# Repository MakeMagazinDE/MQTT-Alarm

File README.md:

Maker Media GmbH

***

# MQTT-Alarm, Make 4/21
Software und Platinen für Alarm-Kontakt und Alarm-Zentrale

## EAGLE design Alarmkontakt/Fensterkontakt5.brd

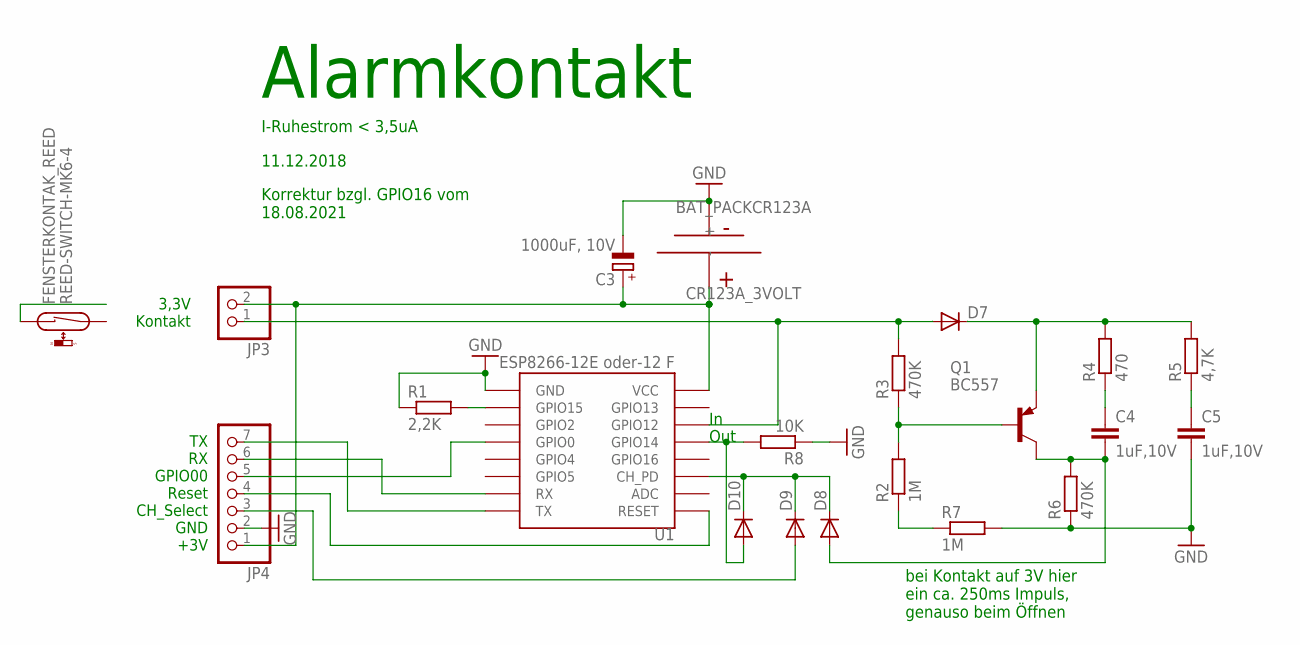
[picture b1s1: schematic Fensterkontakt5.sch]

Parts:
C3: 1000uF, 10V; E5-4
C4, C5: 1uF,10V; C075-032X103
CR123A_3VOLT: BAT_PACKCR123A; BH123A
D7, D8, D9, D10: DIODE-D-7.5; D-7.5
FENSTERKONTAK_REED: REED-SWITCH-MK6-4; MK6-4
JP3: PINHD-1X2; 1X02
JP4: PINHD-1X7; 1X07
Q1: BC557; TO92-EBC
R1: 2,2K; 0207/7
R2, R7: 1M; 0207/7
R3, R6: 470K; 0207/7
R4: 470; 0207/7
R5: 4,7K; 0207/7
R8: 10K; 0207/7
U1: ESP8266-12E oder-12 F; ESP12

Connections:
GND: C3.-, C5.2, CR123A_3VOLT.-, JP4.2, R1.1, R6.1, R7.2, R8.1, U1.GND
unnamed: C4.2, D8.A, Q1.C, R6.2
unnamed: D7.C, Q1.E, R4.2, R5.2
unnamed: C5.1, R5.1
unnamed: JP4.7, U1.TX
unnamed: Q1.B, R2.2, R3.1
unnamed: D8.C, D9.C, D10.C, U1.CH_PD
unnamed: C4.1, R4.1
unnamed: D10.A, R8.2, U1.GPIO14
unnamed: JP4.6, U1.RX
unnamed: D7.A, JP3.1, R3.2, U1.GPIO12
unnamed: R1.2, U1.GPIO15
unnamed: JP4.4, U1.RESET
unnamed: D9.A, JP4.3
unnamed: C3.+, CR123A_3VOLT.+, JP3.2, JP4.1, U1.VCC
unnamed: R2.1, R7.1
unnamed: JP4.5, U1.GPIO0

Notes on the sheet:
3,3V Kontakt
I-Ruhestrom < 3,5uA
Alarmkontakt
11.12.2018
TX RX GPIO00 Reset CH_Select GND +3V
bei Kontakt auf 3V hier ein ca. 250ms Impuls, genauso beim Öffnen
Out
Korrektur bzgl. GPIO16 vom 18.08.2021

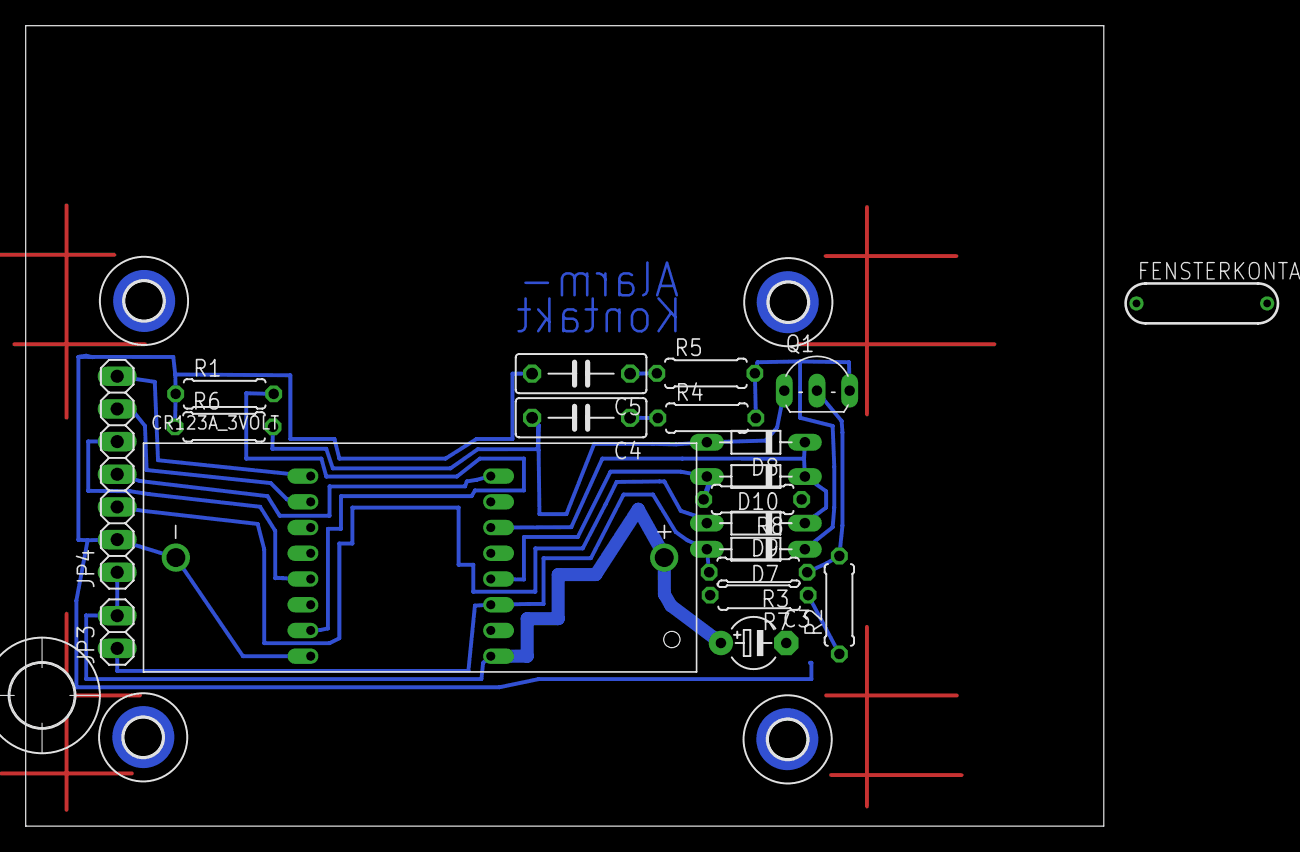
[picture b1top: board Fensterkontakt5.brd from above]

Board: 2 copper layers, 83.8 x 62.2 mm, 26 parts (1 on the bottom side), 17 nets.

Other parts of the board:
U$1: 5,0
U$2, U$3, U$4, U$5: 3,0

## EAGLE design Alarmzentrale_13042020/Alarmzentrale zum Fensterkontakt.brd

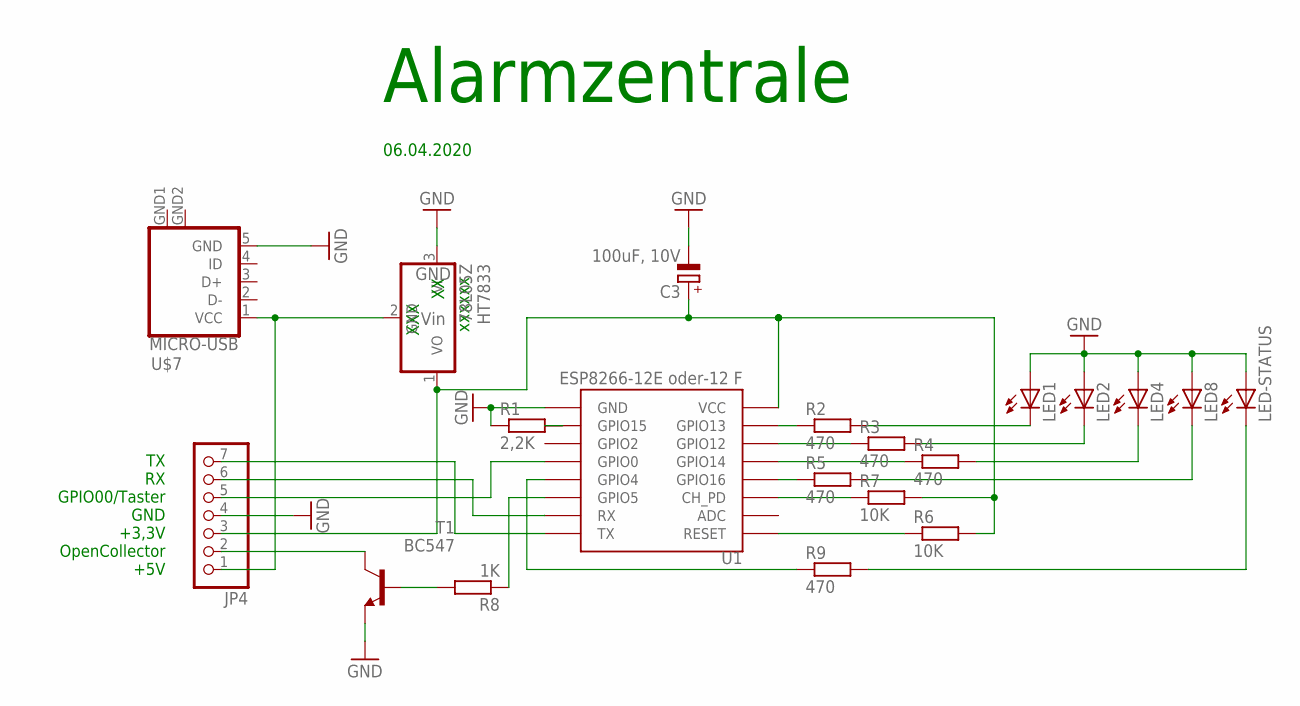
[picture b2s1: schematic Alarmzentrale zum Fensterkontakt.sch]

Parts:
C3: 100uF, 10V; E5-4
HT7833: 78L05Z; TO92
JP4: PINHD-1X7; 1X07
LED1, LED2, LED4, LED8: LED_ELD260; LED_LD260
LED-STATUS: LED_ELD260; LED_LD260
R1: 2,2K; 0207/7
R2, R3, R4, R5, R9: 470; 0207/7
R6, R7: 10K; 0207/7
R8: 1K; 0207/7
T1: BC547; TO92L
U1: ESP8266-12E oder-12 F; ESP12
U$7: MICRO-USB

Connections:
GND: C3.-, HT7833.3 (VI), JP4.4, LED1.A, LED2.A, LED4.A, LED8.A, LED-STATUS.A, R1.1, T1.1 (E), U1.GND, U$7.5 (GND), U$7.GND1 (GND), U$7.GND2 (GND)
unnamed: C3.+, HT7833.1 (VO), JP4.3, R6.2, R7.2, U1.VCC
unnamed: R2.1, U1.GPIO13
unnamed: R3.1, U1.GPIO12
unnamed: JP4.7, U1.TX
unnamed: R4.1, U1.GPIO14
unnamed: R5.1, U1.GPIO16
unnamed: R7.1, U1.CH_PD
unnamed: R6.1, U1.RESET
unnamed: R8.2, T1.2 (B)
unnamed: JP4.6, U1.RX
unnamed: LED1.K (C), R2.2
unnamed: R1.2, U1.GPIO15
unnamed: LED2.K (C), R3.2
unnamed: LED4.K (C), R4.2
unnamed: LED8.K (C), R5.2
unnamed: R9.1, U1.GPIO4
unnamed: HT7833.2 (GND), JP4.1, U$7.1 (VCC)
unnamed: JP4.2, T1.3 (C)
unnamed: LED-STATUS.K (C), R9.2
unnamed: R8.1, U1.GPIO5
unnamed: JP4.5, U1.GPIO0

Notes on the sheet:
Alarmzentrale
06.04.2020
TX RX GPIO00/Taster GND +3,3V OpenCollector +5V
GND
Vin
xxxxxx
XXX

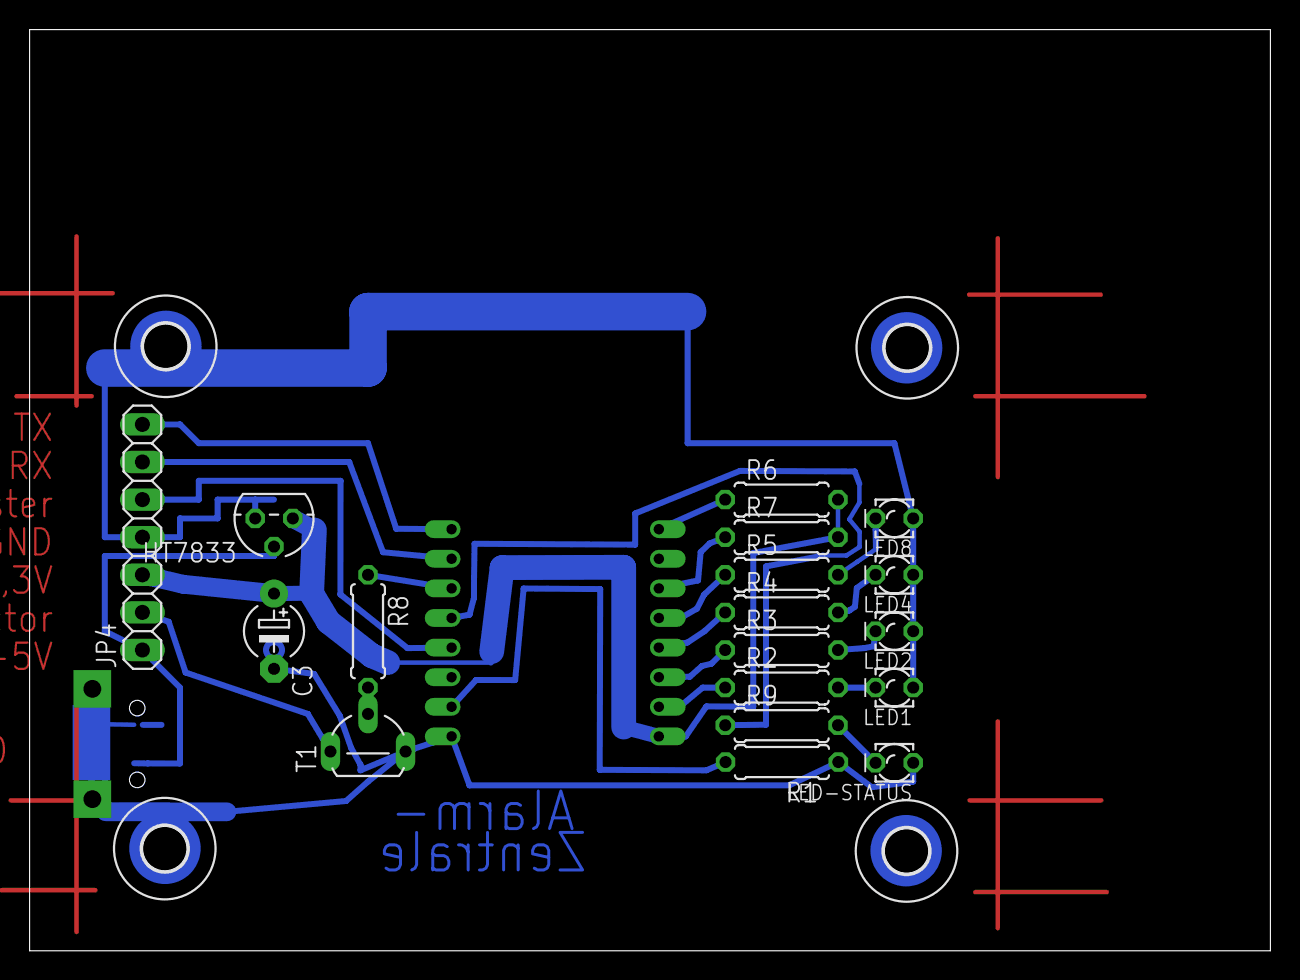
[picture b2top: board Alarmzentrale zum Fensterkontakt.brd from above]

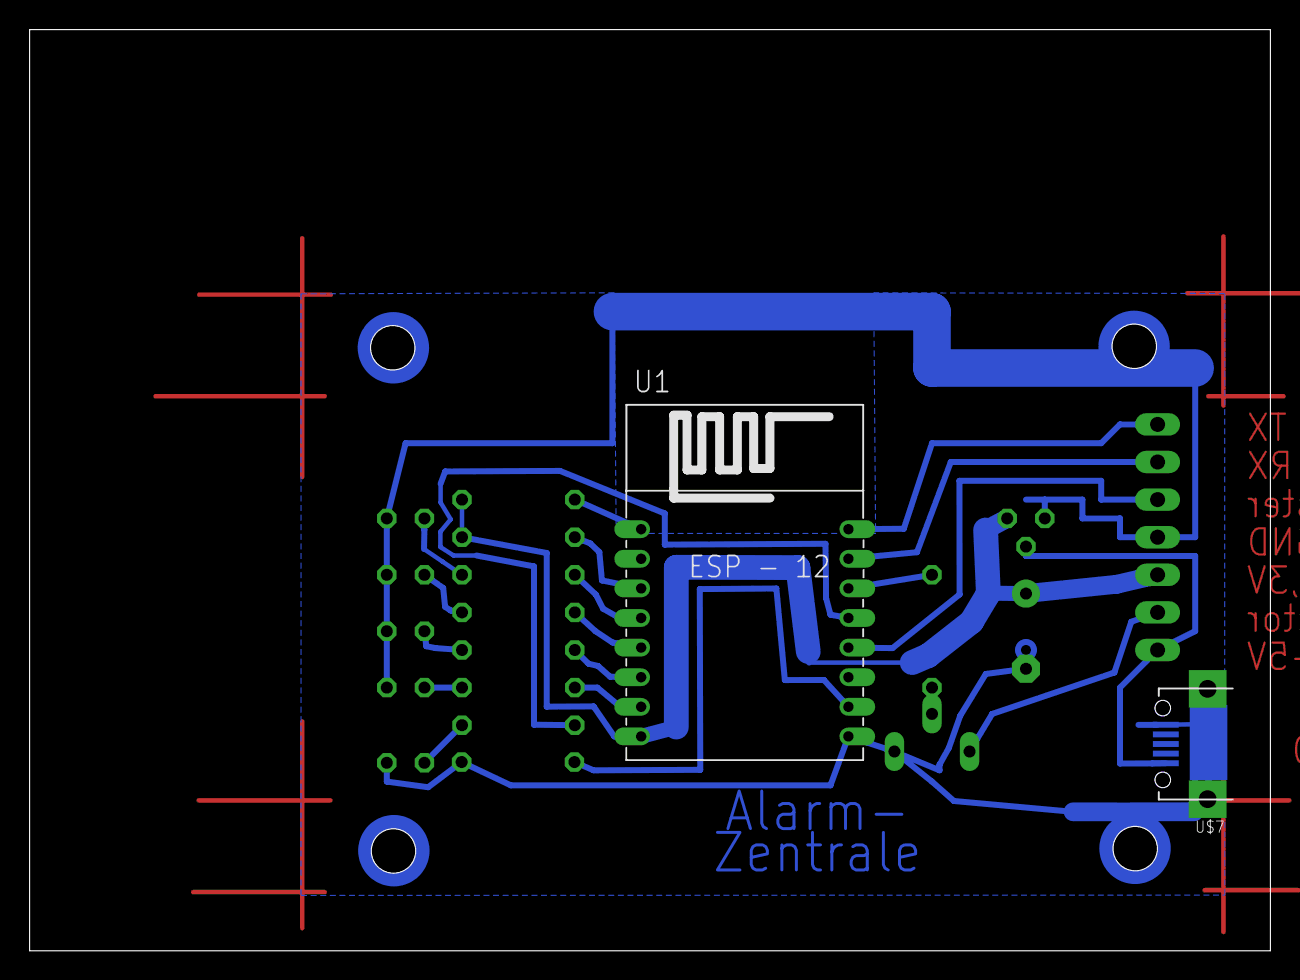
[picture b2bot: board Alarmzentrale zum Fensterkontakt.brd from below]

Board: 2 copper layers, 83.8 x 62.2 mm, 24 parts (2 on the bottom side), 22 nets.

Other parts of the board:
U$2, U$3, U$4, U$5: 3,0

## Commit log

2021-09-09 Fehler in Zusammenhang mit GPIO16 behoben
